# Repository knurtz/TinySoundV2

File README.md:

# TinySound V2
Version two of [TinySound](https://github.com/knurtz/TinySound), a miniature audio module with a 3W class-D audio amplifier.

Instead of an SD card slot as version one, this module features a micro-USB port and presents itself as a mass storage device. Sound files and config data can easily be uploaded from any computer that supports FAT12 file systems.

## Parts list

- RaspberryPi RP2040 microcontroller
- MAX98360 class-D audio amp with I2S interface
- 16 MB of onboard flash

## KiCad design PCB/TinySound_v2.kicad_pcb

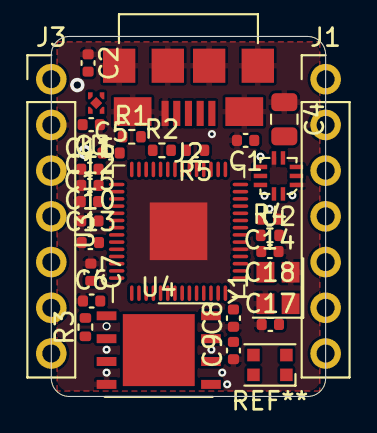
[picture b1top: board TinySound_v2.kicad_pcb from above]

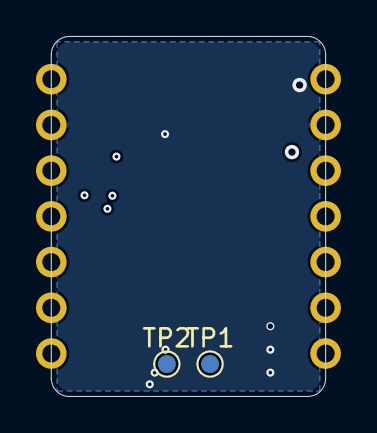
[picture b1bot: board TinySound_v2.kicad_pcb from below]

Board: 4 copper layers, 15.2 x 20.0 mm, 32 parts (2 on the bottom side), 33 nets, no tracks yet.

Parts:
C1, C5, C6, C7, C8, C9, C10, C13, C14, C16: 100n; C_0402_1005Metric
C2, C3, C12, C15: 1u; C_0402_1005Metric
C4: 10u; C_0805_2012Metric
C17, C18: 27p; C_0402_1005Metric
J1, J3: Conn_01x07; PinHeader_1x07_P2.54mm_Vertical
J2: USB_B_Micro; USB_Micro-B_Amphenol_10104110_Horizontal
R1, R2: 27R; R_0402_1005Metric
R3, R4: 1k; R_0402_1005Metric
R5: 10k; R_0402_1005Metric
TP1, TP2: TestPoint; TestPoint_Pad_D1.0mm
U1: MIC5504-3.3YMT; OnSemi_XDFN4-1EP_1.0x1.0mm_EP0.52x0.52mm
U2: MAX98360AEFB+T; FC2QFN-10
U3: RP2040; QFN-56_EP_7x7_Pitch0.4mm
U4: W25Q128JVS; DFN-8-1EP_6x5mm_P1.27mm_EP4x4mm
Y1: 12M; Crystal_SMD_2520-4Pin_2.5x2.0mm

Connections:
+3V3: C3.2, C5.2, C6.2, C7.2, C8.2, C9.2, C10.2, C12.2, C16.2, J3.1, R5.2, U1.1 (VOUT), U3.1 (IOVDD), U3.10 (IOVDD), U3.22 (IOVDD), U3.33 (IOVDD), U3.42 (IOVDD), U3.43 (ADC_AVDD), U3.44 (VREG_VIN), U3.48 (USB_VDD), U3.49 (IOVDD), U4.8 (VCC)
+5V: C1.1, C2.2, C4.2, J1.1, J2.1 (VBUS), U1.4 (VIN), U2.4 (VDD)
/+1V1: C13.2, C14.2, C15.2, U3.23 (DVDD), U3.45 (VREG_VOUT), U3.50 (DVDD)
/AU_BCLK: U2.8 (DAI2), U3.36 (GPIO24)
/AU_DIN: U2.10 (DAI1), U3.34 (GPIO22)
/AU_EN: U2.6 (EN), U3.37 (GPIO25)
/AU_LRCLK: U2.9 (DAI0), U3.35 (GPIO23)
/GPIO1: J1.5, U3.30 (GPIO19)
/GPIO2: J1.6, U3.29 (GPIO18)
/GPIO3: J1.7, U3.40 (GPIO28/ADC2)
/GPIO4: J3.4, U3.8 (GPIO6)
/GPIO5: J3.3, U3.5 (GPIO3)
/OUTN: J1.3, U2.3 (OUTN)
/OUTP: J1.4, U2.2 (OUTP)
/QSPI_SCLK: U3.52 (QSPI_SCLK), U4.6 (CLK)
/QSPI_SD0: U3.53 (QSPI_SD0), U4.5 (DI(IO0))
/QSPI_SD1: U3.55 (QSPI_SD1), U4.2 (DO(IO1))
/QSPI_SD2: U3.54 (QSPI_SD2), U4.3 (IO2)
/QSPI_SD3: U3.51 (QSPI_SD3), U4.7 (IO3)
/QSPI_SS: R3.2, U3.56 (QSPI_SS_N), U4.1 (~CS)
/RUN: J3.7, R5.1, U3.26 (RUN)
/SWCLK: TP2.1, U3.24 (SWCLK)
/SWDIO: TP1.1, U3.25 (SWDIO)
/UART_RX: J3.6, U3.7 (GPIO5)
/UART_TX: J3.5, U3.6 (GPIO4)
/USB_DM: R2.1, U3.46 (USB_DM)
/USB_DP: R1.1, U3.47 (USB_DP)
/XIN: C18.2, U3.20 (XIN), Y1.3
/XOUT: R4.1, U3.21 (XOUT)
GND: C1.2, C2.1, C3.1, C4.1, C5.1, C6.1, C7.1, C8.1, C9.1, C10.1, C12.1, C13.1, C14.1, C15.1, C16.1, C17.1, C18.1, J1.2, J2.5 (GND), J2.6 (Shield), J3.2, U1.2 (GND), U1.5, U2.1 (GND), U2.5 (GND), U3.19 (TESTEN), U3.57 (GND), U4.4 (GND), Y1.2, Y1.4
unnamed: C17.2, R4.2, Y1.1
unnamed: J2.2 (D-), R2.2
unnamed: J2.3 (D+), R1.2

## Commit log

2022-04-23 Copied project structure from TinySound v1
2022-04-23 Added library for RP2040, added gitignore
2022-04-23 Added all components in schematic
2022-04-23 RP2040 power, flash, crystal and reset
2022-04-23 Finished first version of schematic
2022-04-23 Added footprints, annoted schematic
2022-05-15 Added first version of PCB
2022-05-15 Added base code for project.
2022-05-15 Added readme
2022-06-05 Shell works
2022-06-05 Added interactive BOM
2022-11-13 Got TinyUSB demo for CDC and MSC working
2022-11-19 Shell works with TinyUSB library now
2022-11-28 Custom mass storage (read only) on special part of flash
2022-12-04 Mass storage working.
2022-12-04 Moved some stuff around, disabled debug outputs for mass storage.
2022-12-05 Added script to auto-generate c_cpp_properties.json for VS Code
2022-12-05 Make now always generates two UF2 (normal / short)
2022-12-05 Disabled interrupts on flash access for safety reasons.
2022-12-05 Tweaked some function names
2022-12-05 VSCode script now outputs cmake stuff into right folder.
2022-12-07 Cleared round traces on PCB, added WS2812 in schematic
2022-12-13 Included queded read to be used instead of memcpy
2022-12-13 Removed old unnecessary stuff
2022-12-13 Added FatFS with custom glue functions for mass storage access
2022-12-16 Mounting mass storage and folder tree works on device
2022-12-18 Increased mass storage size to 16 MB, fixed UF2 modification
2022-12-18 Added read file command
2023-02-19 Moved some functions around, added testsounds
2023-02-20 Implemented first version of audio playback
2023-02-20 Some audio fixes
2023-02-22 Audio works
2023-02-23 Removed old code snippets, added comments
2023-02-23 Implemented audio stop command
2023-02-23 Added auto play triggered by GPIO
2023-04-03 New component arrangement vor v2.1
2023-04-03 Moved components to better positions
